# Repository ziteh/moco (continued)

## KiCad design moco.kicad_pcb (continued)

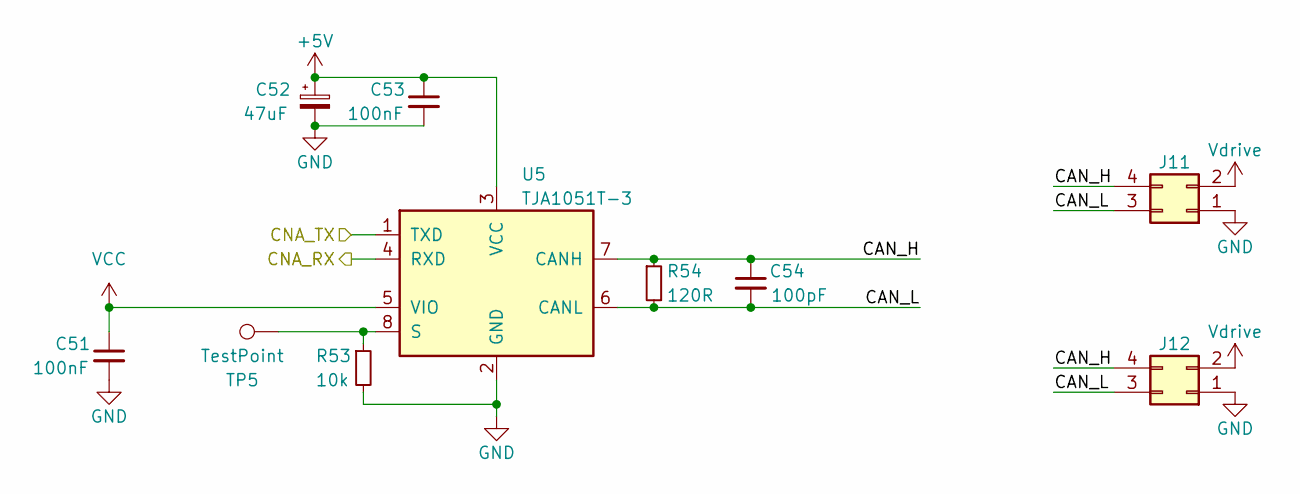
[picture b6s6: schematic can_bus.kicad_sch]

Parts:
C51, C53: 100nF; C_0402_1005Metric; MFR.Part # CL05B104KO5NNNC; JLCPCB Part # C1525
C52: 47uF; C_0402_1005Metric
C54: 100pF; C_0402_1005Metric
J11, J12: Conn_02x02_Top_Bottom; Molex 43045-0406 Micro-Fit 3.0 2x02P; MFR.Part # 430450406; JLCPCB Part # C505218
R53: 10k; R_0402_1005Metric; MFR.Part # 0402WGF1002TCE; JLCPCB Part # C25744
R54: 120R; R_0402_1005Metric; MFR.Part # 0402WGF1200TCE; JLCPCB Part # C25079
TP5: TestPoint; TestPoint_Pad_D2.0mm
U5: TJA1051T-3; SOIC-8_3.9x4.9mm_P1.27mm; MFR.Part # TJA1051T/3/1J; JLCPCB Part # C38695

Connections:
+5V: C52.1, C53.1, U5.3 (VCC); also elsewhere on the board
/CAN BUS/CAN_H: C54.1, J11.4, J12.4, R54.1, U5.7 (CANH)
/CAN BUS/CAN_L: C54.2, J11.3, J12.3, R54.2, U5.6 (CANL)
/CNA_RX: U5.4 (RXD); also elsewhere on the board
/CNA_TX: U5.1 (TXD); also elsewhere on the board
unnamed: R53.1, TP5.1, U5.8 (S)
VCC: C51.1, U5.5 (VIO); also elsewhere on the board

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
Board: 4 copper layers, 203 parts (36 on the bottom side), 150 nets, no tracks yet.

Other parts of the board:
C58: 1uF; C_0402_1005Metric
C59: 100nF; C_0402_1005Metric
J10: Conn_01x03; AMASS MR30PB-F
J13: Conn_01x02; PhoenixContact_GMSTBA_2,5_2-G-7,62_1x02_P7.62mm_Horizontal
R60, R61, R62: 10k; R_0402_1005Metric
U7: AS5047x; TSSOP-14_4.4x5mm_P0.65mm

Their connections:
/AS5047x_A: U7.7 (A); also elsewhere on the board
/AS5047x_B: U7.6 (B); also elsewhere on the board
/AS5047x_I: U7.14 (I/PWM); also elsewhere on the board
/Motor Driver/SH_A: J10.1; also elsewhere on the board
/Motor Driver/SH_B: J10.2; also elsewhere on the board
/Motor Driver/SH_C: J10.3; also elsewhere on the board
/SPI_CLK: R61.1, U7.2 (CLK); also elsewhere on the board
/SPI_MISO: U7.3 (MISO); also elsewhere on the board
/SPI_MOSI: R60.1, U7.4 (MOSI); also elsewhere on the board
/SPI_~CS_AS5047x: R62.2, U7.1 (~CS); also elsewhere on the board
unnamed 104: J13.1; also elsewhere on the board
VCC: C58.1, C59.1, R62.1, U7.11 (VDD), U7.12 (VDD3V3); also elsewhere on the board
